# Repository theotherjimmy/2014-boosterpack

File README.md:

2014-boosterpack
================
This repo contains the eagle source for a boosterpack designed for the Stellaris/Tiva lm4f/tm4c launchpads.

Features
================
* buck regulator circuit for bat -> vbus of launchpad
* headers for the launchpad
* motor driver circuit for driving two motors from battery power
* headers of power, ground, signal trios for ports B,D,E

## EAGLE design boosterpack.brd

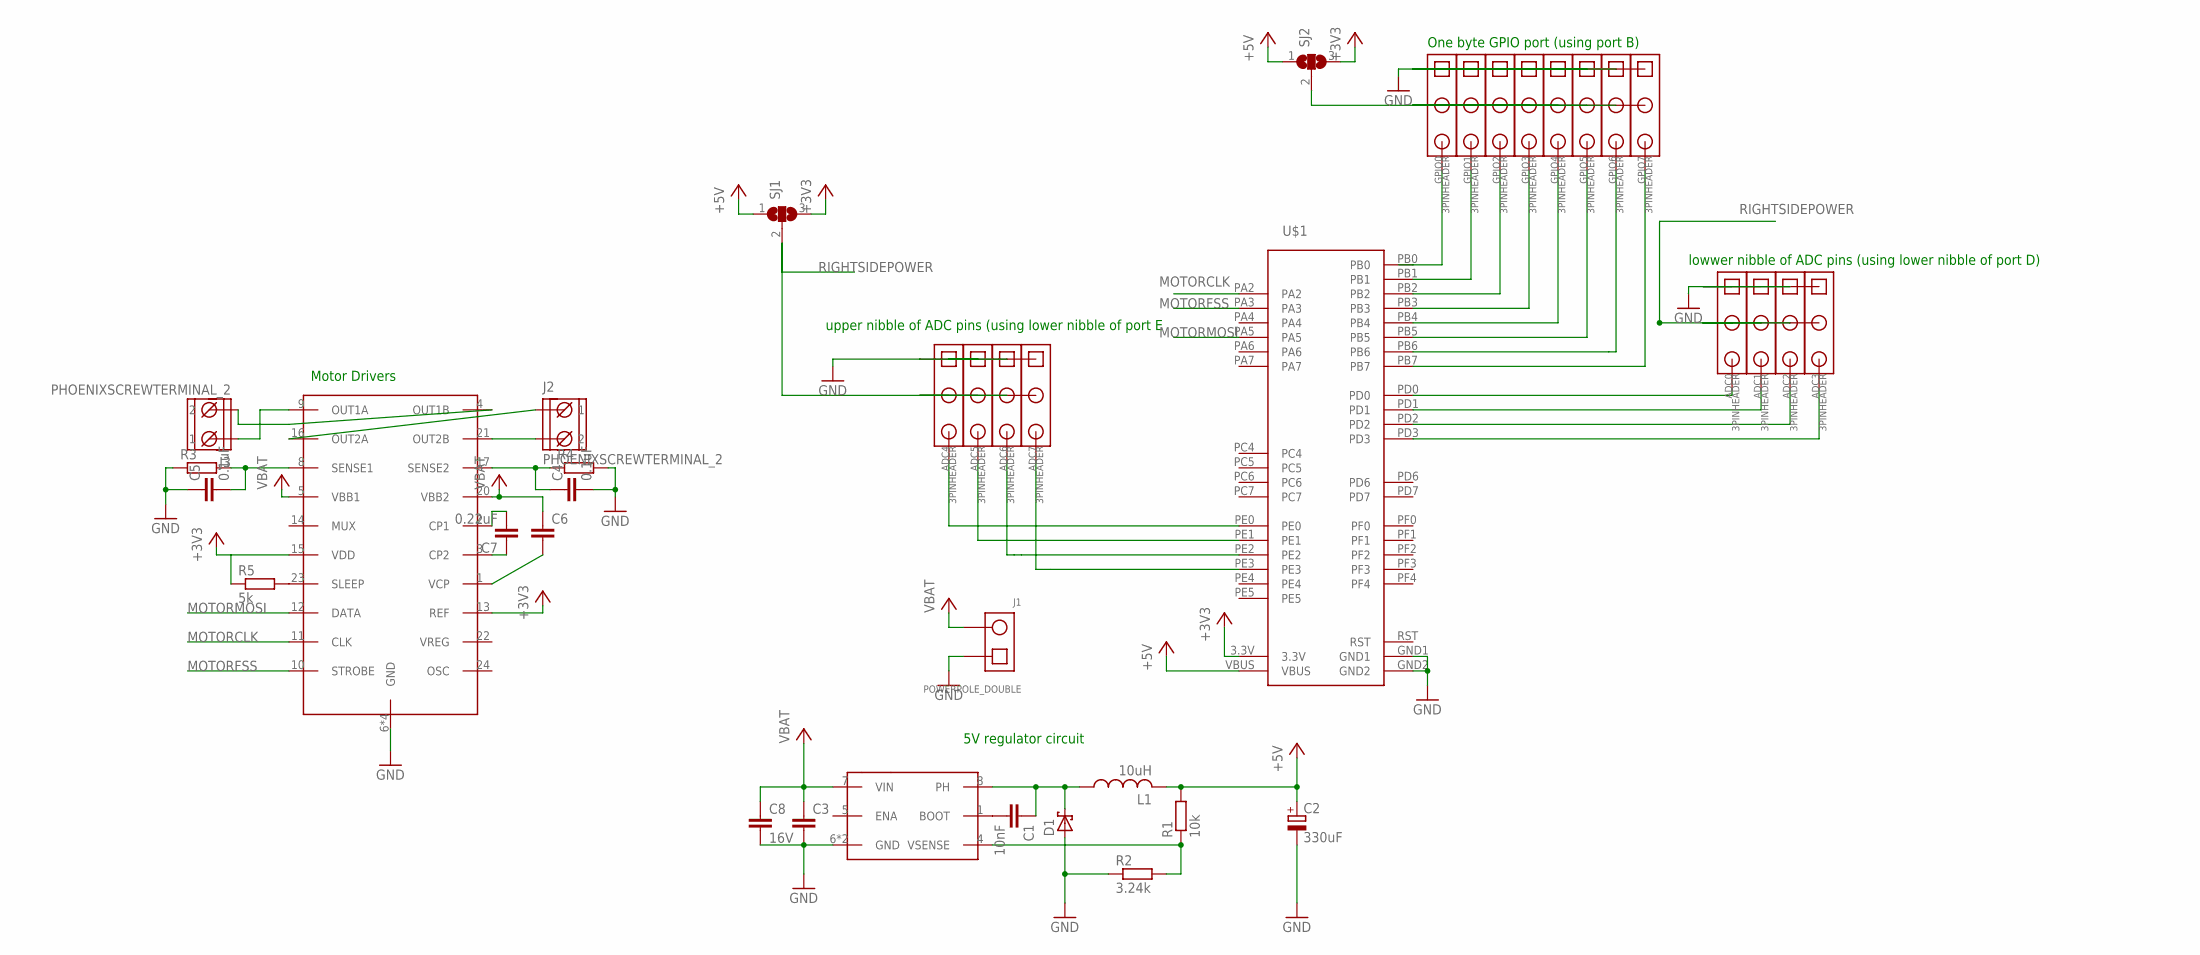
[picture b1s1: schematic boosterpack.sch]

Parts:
ADC0, ADC1, ADC2, ADC3, ADC4, ADC5, ADC6, ADC7: 3PINHEADER
C1: 10nF; C025-024X044
C2: 330uF; B45181B
C3: C-EU025-024X044; C025-024X044
C4, C5: 0.1uF; C025-025X050
C6: C-EU025-025X050; C025-025X050
C7: 0.22uF; C025-024X044
C8: 16V; C050-075X075
D1: SCHOTTKY-DIODEDO201T15; DO201T15
GPIO0, GPIO1, GPIO2, GPIO3, GPIO4, GPIO5, GPIO6, GPIO7: 3PINHEADER
J1: POWERPOLE_DOUBLE
J2, J3: PHOENIXSCREWTERMINAL_2
L1: 10uH; SDR1006
R1: 10k; 0204/7
R2: 3.24k; 0204/7
R3, R4: R-EU_0204/7; 0204/7
R5: 5k; 0204/7
SJ1, SJ2: SJ2W; SJ_2
U$1: STELLARIS-LAUNCHPADSTELLARIS-LAUNCHPAD-XL; LAUNCHPAD-XL
U$2: TPS5450; DDS
U$3: A3992A; DIP24

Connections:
+3V3: R5.1, SJ1.3, SJ2.3, U$1.3.3V, U$3.13 (REF), U$3.15 (VDD)
+5V: C2.+, L1.P$2 (2), R1.2, SJ1.1, SJ2.1, U$1.VBUS
ADC1: ADC1.3, U$1.PD1
ADC2: ADC2.3, U$1.PD2
ADC3: ADC3.3, U$1.PD3
ADC5: ADC5.3, U$1.PE1
GND: ADC0.1, ADC1.1, ADC2.1, ADC3.1, ADC4.1, ADC5.1, ADC6.1, ADC7.1, C2.-, C3.2, C4.2, C5.1, C8.2, D1.A, GPIO0.1, GPIO1.1, GPIO2.1, GPIO3.1, GPIO4.1, GPIO5.1, GPIO6.1, GPIO7.1, J1.1, R2.1, R3.1, R4.2, U$1.GND1, U$1.GND2, U$2.6 (GND), U$2.GROUNDPAD (GND), U$3.6 (GND), U$3.7 (GND), U$3.18 (GND), U$3.19 (GND)
GPIO0: GPIO0.3, U$1.PB0
GPIO1: GPIO1.3, U$1.PB1
GPIO2: GPIO2.3, U$1.PB2
GPIO3: GPIO3.3, U$1.PB3
MOTORCLK: U$1.PA2, U$3.11 (CLK)
MOTORFSS: U$1.PA3, U$3.10 (STROBE)
MOTORMOSI: U$1.PA5, U$3.12 (DATA)
unnamed: ADC0.3, U$1.PD0
unnamed: GPIO4.3, U$1.PB4
unnamed: GPIO5.3, U$1.PB5
unnamed: ADC6.3, U$1.PE2
unnamed: ADC7.3, U$1.PE3
unnamed: GPIO6.3, U$1.PB6
unnamed: GPIO0.2, GPIO1.2, GPIO2.2, GPIO3.2, GPIO4.2, GPIO5.2, GPIO6.2, GPIO7.2, SJ2.2
unnamed: GPIO7.3, U$1.PB7
unnamed: C1.2, U$2.1 (BOOT)
unnamed: R1.1, R2.2, U$2.4 (VSENSE)
unnamed: C1.1, D1.C, L1.P$1 (1), U$2.8 (PH)
unnamed: ADC4.3, U$1.PE0
unnamed: J3.2, U$3.4 (OUT1B)
unnamed: J3.1, U$3.9 (OUT1A)
unnamed: J2.1, U$3.16 (OUT2A)
unnamed: J2.2, U$3.21 (OUT2B)
unnamed: C5.2, R3.2, U$3.8 (SENSE1)
unnamed: C4.1, R4.1, U$3.17 (SENSE2)
unnamed: C6.2, U$3.1 (VCP)
unnamed: R5.2, U$3.23 (SLEEP)
unnamed: C7.1, U$3.3 (CP2)
unnamed: C7.2, U$3.2 (CP1)
RIGHTSIDEPOWER: ADC0.2, ADC1.2, ADC2.2, ADC3.2, ADC4.2, ADC5.2, ADC6.2, ADC7.2, SJ1.2
RST: U$1.RST
VCC: C3.1, C6.1, C8.1, J1.2, U$2.7 (VIN), U$3.5 (VBB1), U$3.20 (VBB2)

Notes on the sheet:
One byte GPIO port (using port B)
lowwer nibble of ADC pins (using lower nibble of port D)
upper nibble of ADC pins (using lower nibble of port E
5V regulator circuit
Motor Drivers

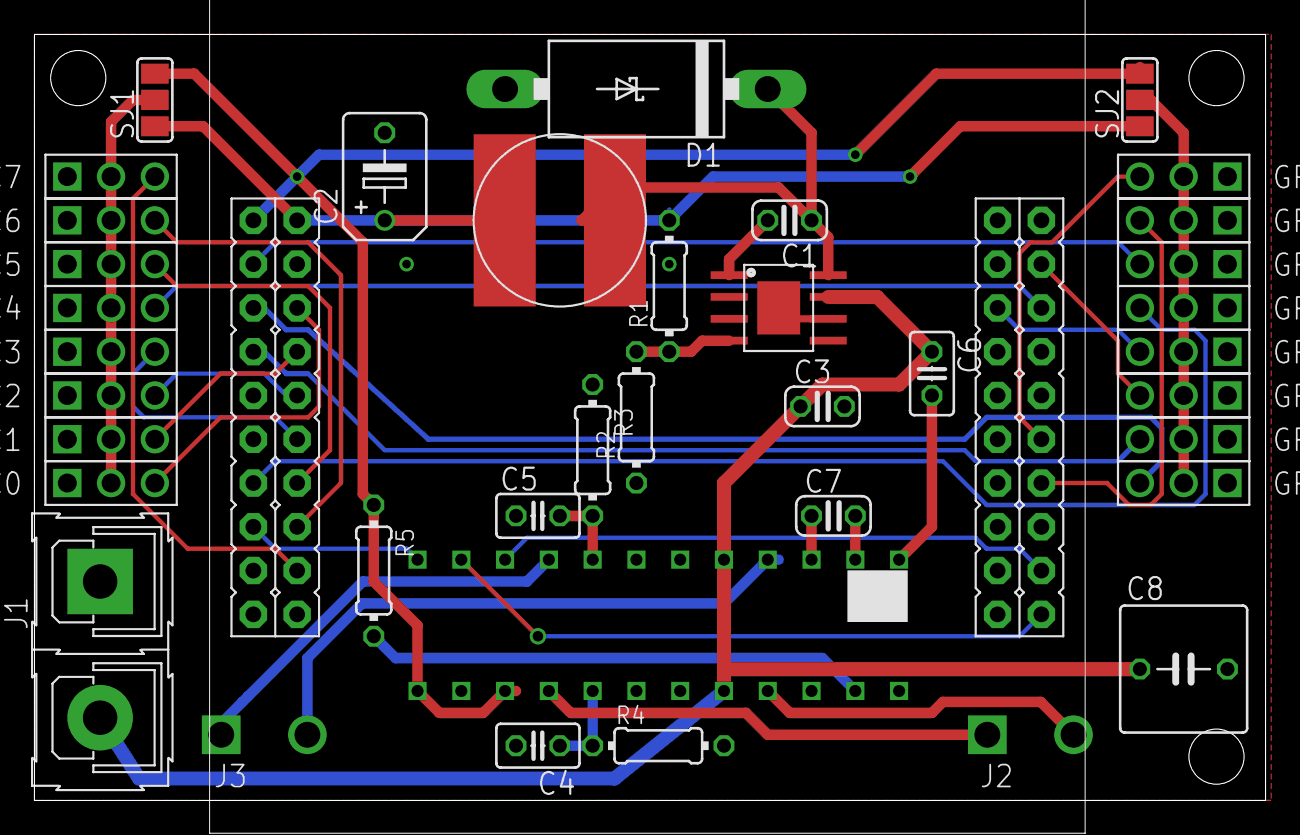
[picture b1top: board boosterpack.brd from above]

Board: 2 copper layers, 71.4 x 44.4 mm, 39 parts (0 on the bottom side), 38 nets.

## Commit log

2014-04-30 moved a resistor that was bothering me
2014-05-01 modified todo list; became feature list
2014-05-03 shrank the board; added decopling cap for power
2014-05-03 had @cmonr look at it; implemented suggestions
2014-05-05 tidied up gerbers
2014-05-05 fixed collision in Power labeling and battery connector
2014-05-19 increased the spacing between the leads of all resistors and some caps
